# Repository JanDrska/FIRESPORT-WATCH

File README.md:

# FIRESPORT-WATCH
OpenSource project based on arduino which allows better time measuring and adds some extras features.

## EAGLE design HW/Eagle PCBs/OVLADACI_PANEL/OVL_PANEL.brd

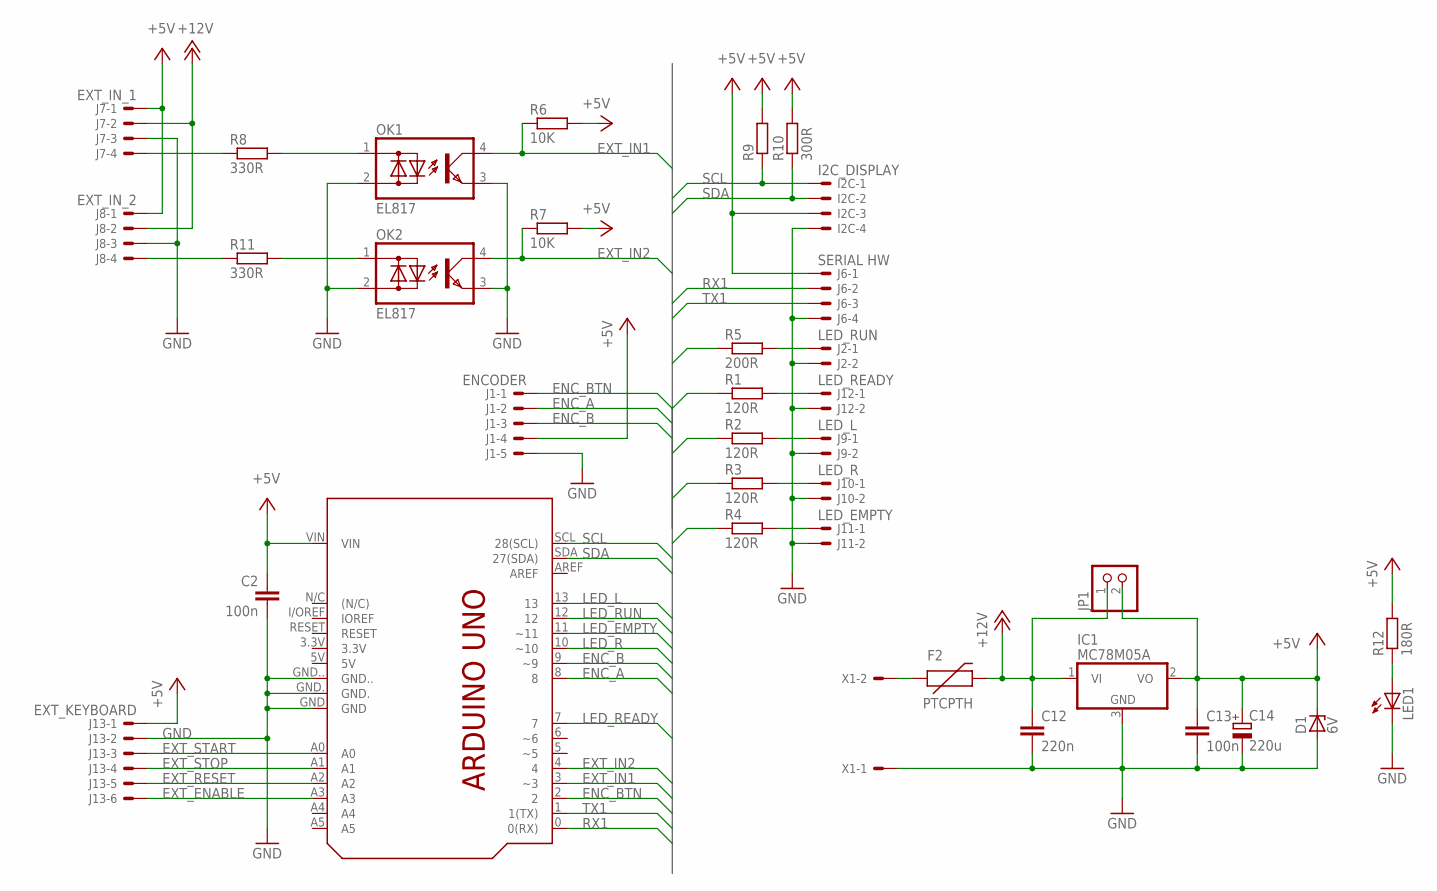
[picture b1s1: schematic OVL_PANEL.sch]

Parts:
C2, C13: 100n; C0603
C12: 220n; C0603
C14: 220u; E2,5-6E
D1: 6V; SMB
F2: PTCPTH; PTC
I2C: I2C_DISPLAY; 6410-04
IC1: MC78M05A; TO252
J1: ENCODER; 6410-05
J2: LED_RUN; 6410-02
J6: SERIAL HW; 6410-04
J7: EXT_IN_1; 6410-04
J8: EXT_IN_2; 6410-04
J9: LED_L; 6410-02
J10: LED_R; 6410-02
J11: LED_EMPTY; 6410-02
J12: LED_READY; 6410-02
J13: EXT_KEYBOARD; 6410-06
JP1: PINHD-1X2; 1X02
LED1: LEDCHIP-LED0603; CHIP-LED0603
OK1, OK2: EL817; DIL04
PCB1: ARDUINO_UNO
R1, R2, R3, R4: 120R; R0603
R5: 200R; R0603
R6, R7: 10K; R0603
R8, R11: 330R; R0603
R9: R-EU_R0603; R0603
R10: 300R; R0603
R12: 180R; R0603
X1: 22-23-2021

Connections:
+5V: C2.1, C13.1, C14.+, D1.C, I2C.3, IC1.2 (VO), J1.4, J6.1, J7.1, J8.1, J13.1, JP1.2, PCB1.VIN, R6.2, R7.2, R9.2, R10.2, R12.2
+12V: C12.1, F2.P$2 (2), IC1.1 (VI), J7.2, J8.2, JP1.1
ENC_A: J1.2, PCB1.8
ENC_B: J1.3, PCB1.9 (~9)
ENC_BTN: J1.1, PCB1.2
EXT_ENABLE: J13.6, PCB1.A3
EXT_IN1: OK1.4 (C), PCB1.3 (~3), R6.1
EXT_IN2: OK2.4 (C), PCB1.4, R7.1
EXT_RESET: J13.5, PCB1.A2
EXT_START: J13.3, PCB1.A0
EXT_STOP: J13.4, PCB1.A1
GND: C2.2, C12.2, C13.2, C14.-, D1.A, I2C.4, IC1.3 (GND), J1.5, J2.2, J6.4, J7.3, J8.3, J9.2, J10.2, J11.2, J12.2, J13.2, LED1.C, OK1.2 (AC2), OK1.3 (E), OK2.2 (AC2), OK2.3 (E), PCB1.GND, PCB1.GND., PCB1.GND.., X1.1
LED_EMPTY: PCB1.11 (~11), R4.1
LED_L: PCB1.13, R2.1
LED_R: PCB1.10 (~10), R3.1
LED_READY: PCB1.7, R1.1
LED_RUN: PCB1.12, R5.1
unnamed: J12.1, R1.2
unnamed: J2.1, R5.2
unnamed: J9.1, R2.2
unnamed: J10.1, R3.2
unnamed: J11.1, R4.2
unnamed: F2.P$1 (1), X1.2
unnamed: J7.4, R8.1
unnamed: J8.4, R11.1
unnamed: LED1.A, R12.1
unnamed: OK2.1 (AC1), R11.2
unnamed: OK1.1 (AC1), R8.2
RX1: J6.2, PCB1.0 (0(RX))
SCL: I2C.1, PCB1.SCL (28(SCL)), R9.1
SDA: I2C.2, PCB1.SDA (27(SDA)), R10.1
TX1: J6.3, PCB1.1 (1(TX))

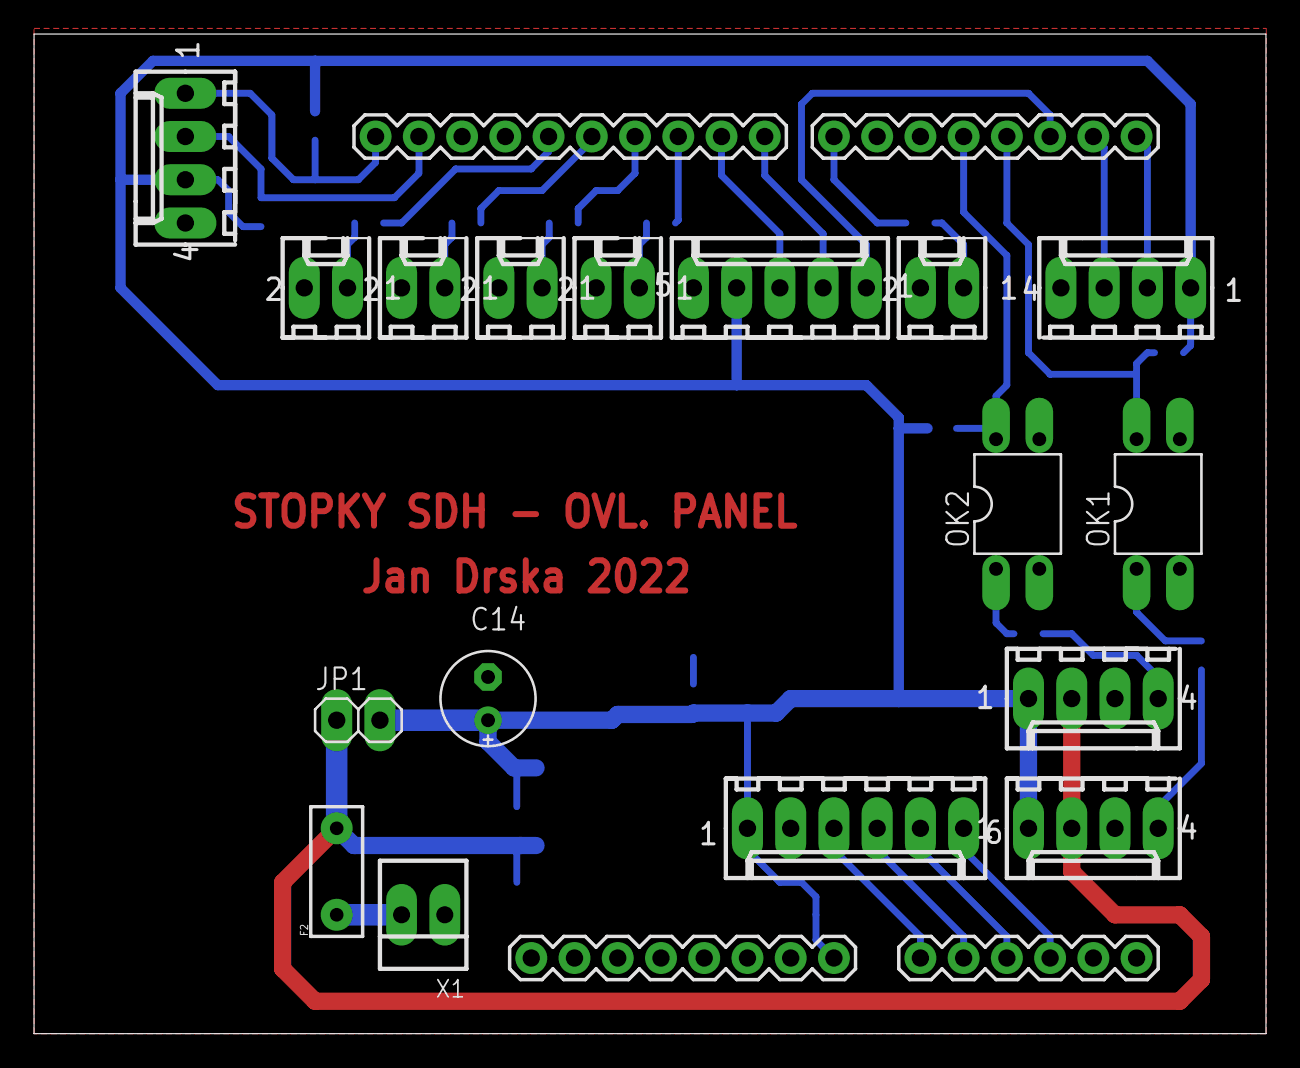
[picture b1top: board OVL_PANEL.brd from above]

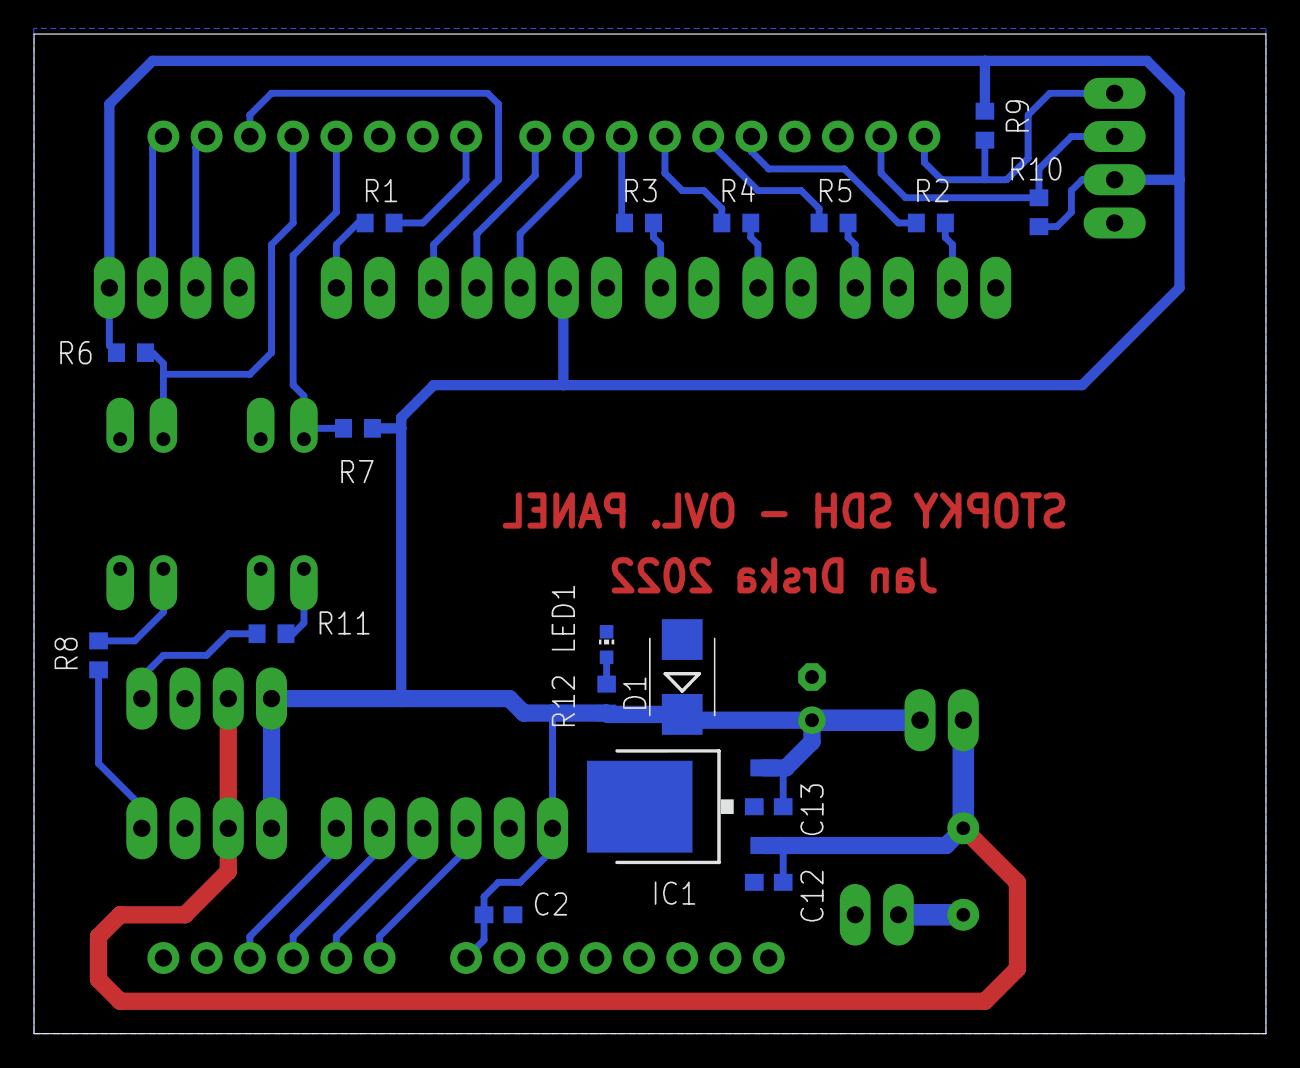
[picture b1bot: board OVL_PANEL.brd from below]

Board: 2 copper layers, 72.4 x 58.7 mm, 36 parts (18 on the bottom side), 32 nets.

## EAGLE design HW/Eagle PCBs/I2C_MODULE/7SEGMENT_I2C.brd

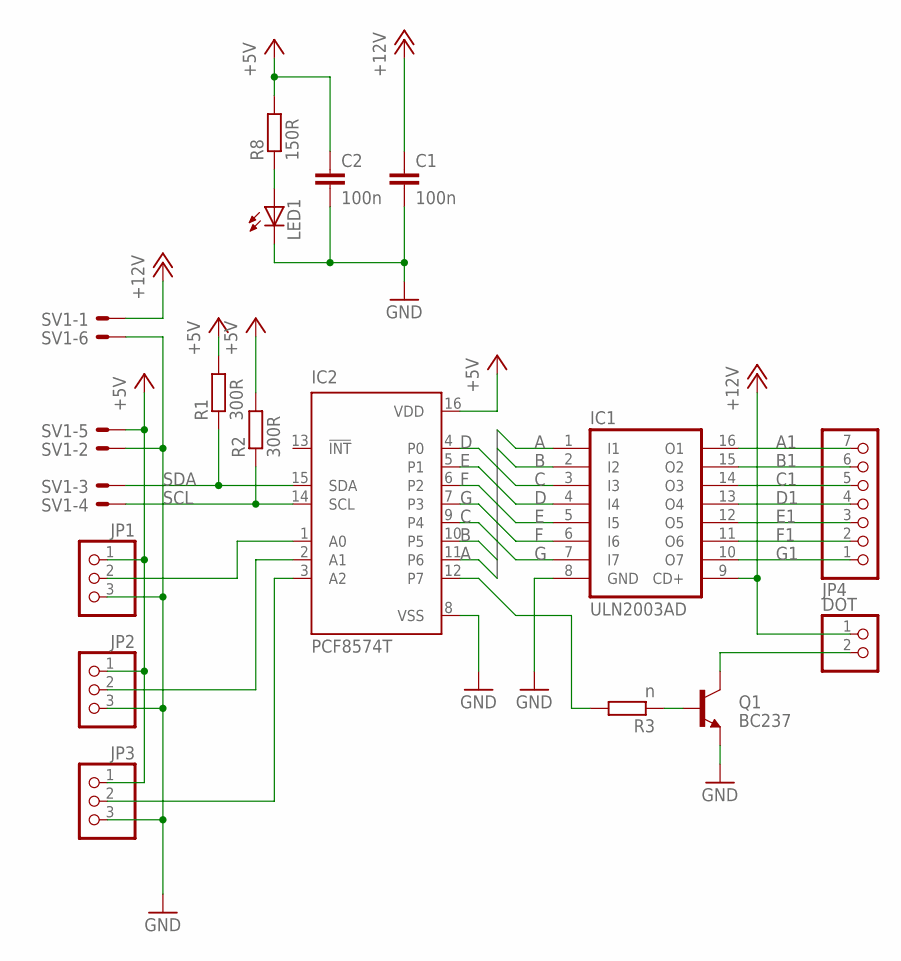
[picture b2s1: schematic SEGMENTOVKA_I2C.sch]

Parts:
C1, C2: 100n; C0603
DOT: PINHD-1X2; 1X02
IC1: ULN2003AD; SO16
IC2: PCF8574T; SO16W
JP1, JP2, JP3: PINHD-1X3; 1X03
JP4: PINHD-1X7; 1X07
LED1: LEDCHIP-LED0603; CHIP-LED0603
Q1: BC237; TO92
R1, R2: 300R; R0603
R3: n; R0603
R8: 150R; R0603
SV1: ML6E; ML6

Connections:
+5V: C2.1, IC2.16 (VDD), JP1.1, JP2.1, JP3.1, R1.2, R2.2, R8.2, SV1.5
+12V: C1.1, DOT.1, IC1.9 (CD+), SV1.1
A: IC1.1 (I1), IC2.11 (P6)
A1: IC1.16 (O1), JP4.7
B: IC1.2 (I2), IC2.10 (P5)
B1: IC1.15 (O2), JP4.6
C: IC1.3 (I3), IC2.9 (P4)
C1: IC1.14 (O3), JP4.5
D: IC1.4 (I4), IC2.4 (P0)
D1: IC1.13 (O4), JP4.4
E: IC1.5 (I5), IC2.5 (P1)
E1: IC1.12 (O5), JP4.3
F: IC1.6 (I6), IC2.6 (P2)
F1: IC1.11 (O6), JP4.2
G: IC1.7 (I7), IC2.7 (P3)
G1: IC1.10 (O7), JP4.1
GND: C1.2, C2.2, IC1.8 (GND), IC2.8 (VSS), JP1.3, JP2.3, JP3.3, LED1.C, Q1.1 (E), SV1.2, SV1.6
unnamed: DOT.2, Q1.3 (C)
unnamed: Q1.2 (B), R3.1
unnamed: IC2.12 (P7), R3.2
unnamed: IC2.1 (A0), JP1.2
unnamed: IC2.2 (A1), JP2.2
unnamed: IC2.3 (A2), JP3.2
unnamed: LED1.A, R8.1
SCL: IC2.14 (SCL), R2.1, SV1.4
SDA: IC2.15 (SDA), R1.1, SV1.3

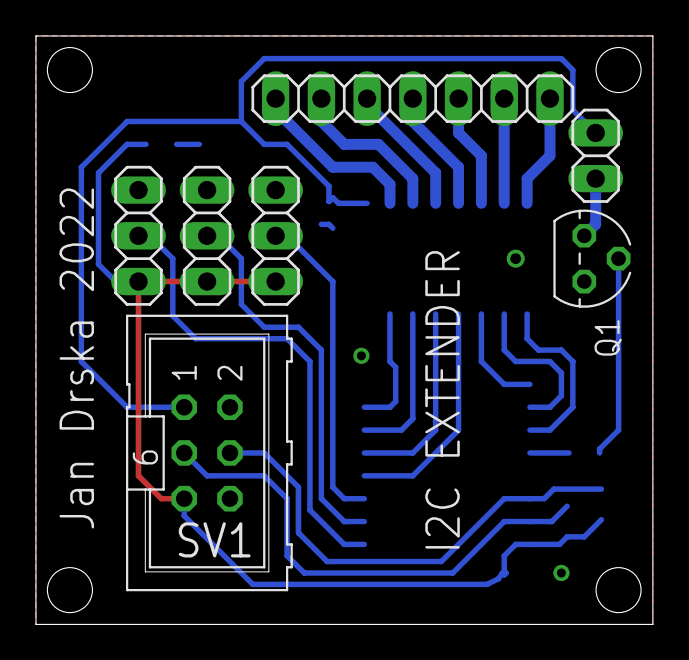
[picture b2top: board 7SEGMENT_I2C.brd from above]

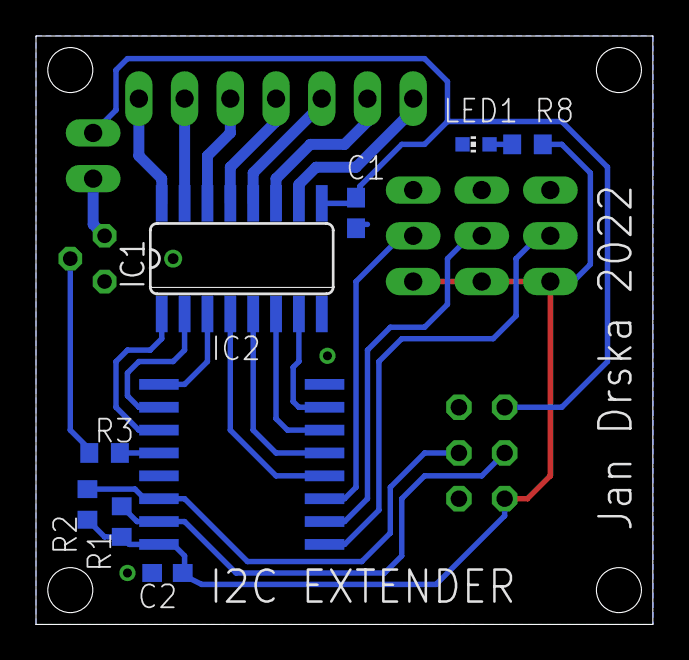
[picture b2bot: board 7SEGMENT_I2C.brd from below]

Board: 2 copper layers, 34.3 x 32.7 mm, 16 parts (9 on the bottom side), 26 nets.

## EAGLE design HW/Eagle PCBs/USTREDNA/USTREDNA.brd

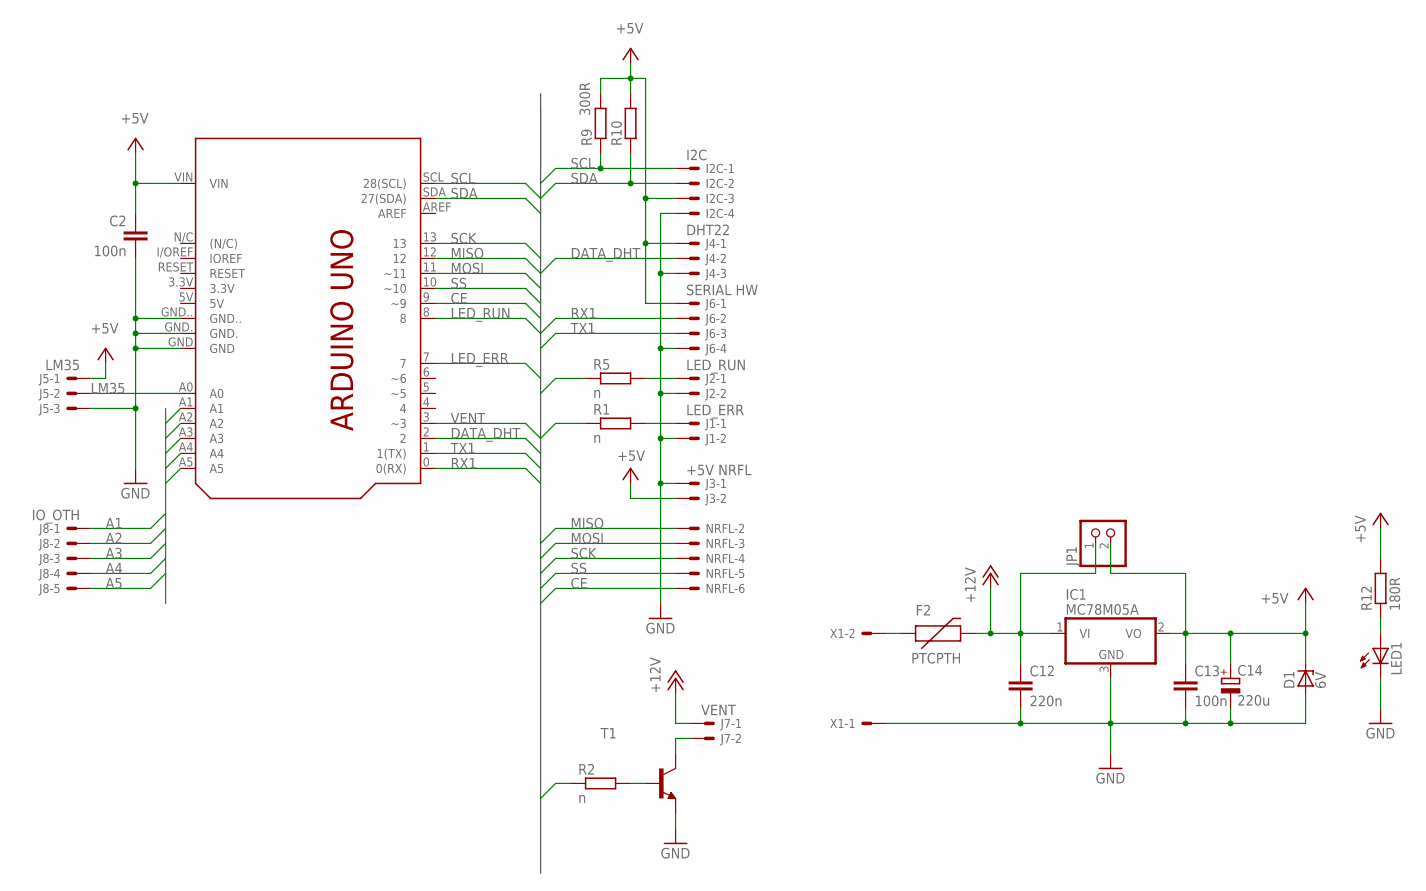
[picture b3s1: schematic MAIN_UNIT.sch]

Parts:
C2, C13: 100n; C0603
C12: 220n; C0603
C14: 220u; E2,5-6E
D1: 6V; SMB
F2: PTCPTH; PTC
I2C: I2C; 6410-04
IC1: MC78M05A; TO252
J1: LED_ERR; 6410-02
J2: LED_RUN; 6410-02
J3: +5V NRFL; 6410-02
J4: DHT22; 6410-03
J5: LM35; 6410-03
J6: SERIAL HW; 6410-04
J7: VENT; 6410-02
J8: IO_OTH; 6410-05
JP1: PINHD-1X2; 1X02
LED1: LEDCHIP-LED0603; CHIP-LED0603
NRFL: NRFL; 6410-06
PCB1: ARDUINO_UNO
R1, R2, R5: n; R0603
R9: R-EU_R0603; R0603
R10: 300R; R0603
R12: 180R; R0603
T1: -NPN-SOT223; SOT223
X1: 22-23-2021

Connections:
+5V: C2.1, C13.1, C14.+, D1.C, I2C.3, IC1.2 (VO), J3.2, J4.1, J5.1, J6.1, JP1.2, PCB1.VIN, R9.2, R10.2, R12.2
+12V: C12.1, F2.P$2 (2), IC1.1 (VI), J7.1, JP1.1
A1: J8.1, PCB1.A1
A2: J8.2, PCB1.A2
A3: J8.3, PCB1.A3
A4: J8.4, PCB1.A4
A5: J8.5, PCB1.A5
CE: NRFL.6, PCB1.9 (~9)
DATA_DHT: J4.2, PCB1.2
GND: C2.2, C12.2, C13.2, C14.-, D1.A, I2C.4, IC1.3 (GND), J1.2, J2.2, J3.1, J4.3, J5.3, J6.4, LED1.C, PCB1.GND, PCB1.GND., PCB1.GND.., T1.3 (E), X1.1
LED_ERR: PCB1.7, R1.1
LED_RUN: PCB1.8, R5.1
LM35: J5.2, PCB1.A0
MISO: NRFL.2, PCB1.12
MOSI: NRFL.3, PCB1.11 (~11)
unnamed: J1.1, R1.2
unnamed: R2.2, T1.1 (B)
unnamed: J2.1, R5.2
unnamed: J7.2, T1.4 (C)
unnamed: F2.P$1 (1), X1.2
unnamed: LED1.A, R12.1
RX1: J6.2, PCB1.0 (0(RX))
SCK: NRFL.4, PCB1.13
SCL: I2C.1, PCB1.SCL (28(SCL)), R9.1
SDA: I2C.2, PCB1.SDA (27(SDA)), R10.1
SS: NRFL.5, PCB1.10 (~10)
TX1: J6.3, PCB1.1 (1(TX))
VENT: PCB1.3 (~3), R2.1

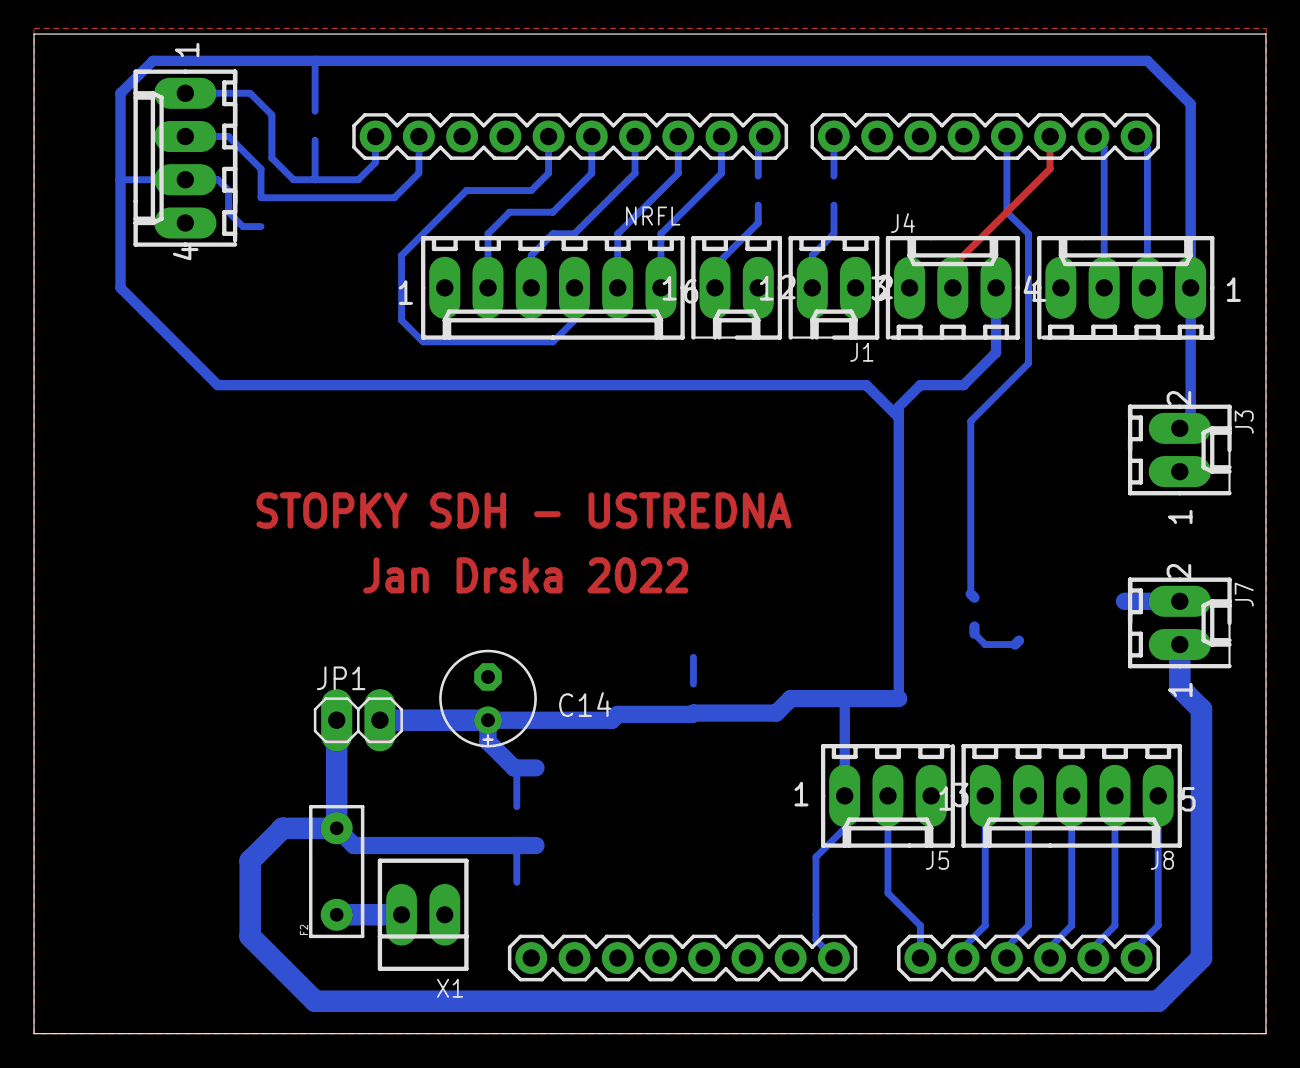
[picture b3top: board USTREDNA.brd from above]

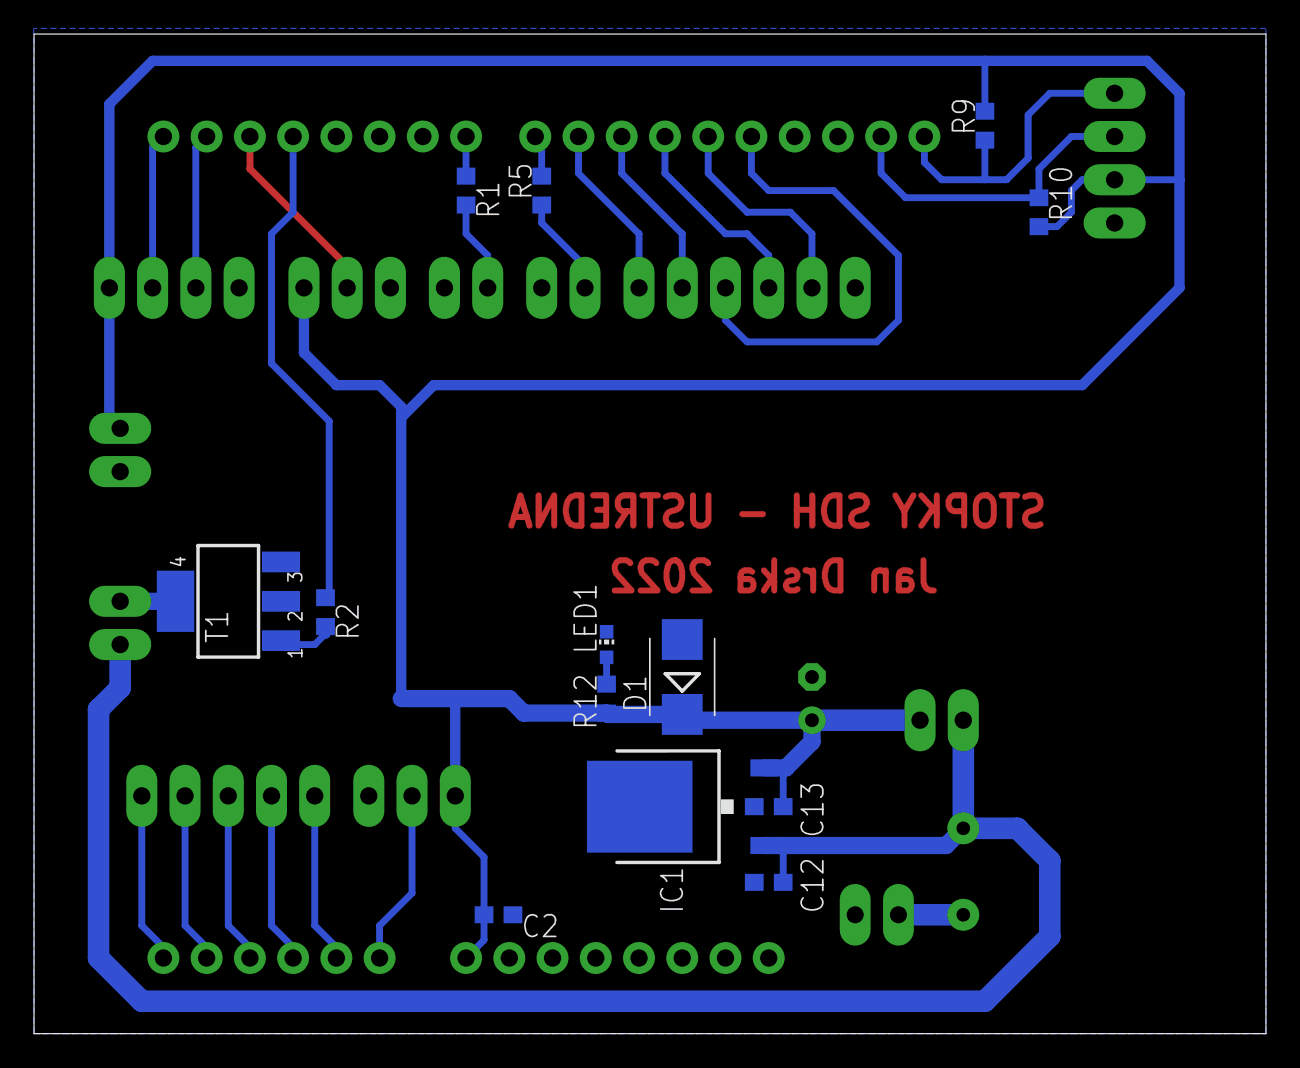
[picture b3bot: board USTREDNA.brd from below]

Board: 2 copper layers, 72.4 x 58.7 mm, 28 parts (13 on the bottom side), 28 nets.

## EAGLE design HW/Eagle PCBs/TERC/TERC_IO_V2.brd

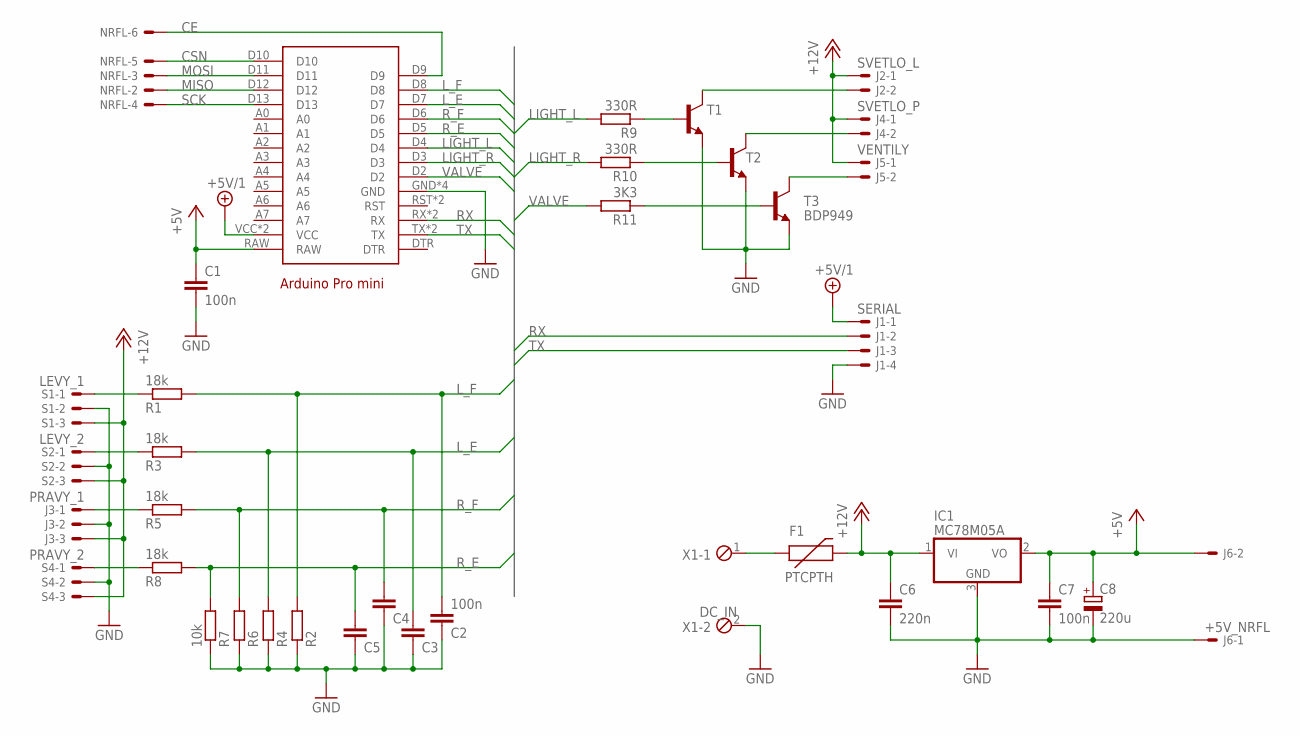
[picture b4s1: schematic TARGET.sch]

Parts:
ARDUINO1: ARDUINO_PRO_MINI
C1, C2, C7: 100n; C0603
C3, C4, C5: C-EUC0603; C0603
C6: 220n; C0603
C8: 220u; E2,5-6E
F1: PTCPTH; PTC
IC1: MC78M05A; TO252
J1: SERIAL; 6410-04
J2: SVETLO_L; 6410-02
J3: PRAVY_1; 6410-03
J4: SVETLO_P; 6410-02
J5: VENTILY; 6410-02
J6: +5V_NRFL; 6410-02
NRFL: NRFL; 6410-06
R1, R3, R5, R8: 18k; R0603
R2, R4, R6: R-EU_R0603; R0603
R7: 10k; R0603
R9, R10: 330R; R0603
R11: 3K3; R0603
S1: LEVY_1; 6410-03
S2: LEVY_2; 6410-03
S4: PRAVY_2; 6410-03
T1, T3: BDP949; SOT223
T2: -NPN-SOT223; SOT223
X1: DC_IN; 2POL254

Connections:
+5V: ARDUINO1.RAW, C1.1, C7.1, C8.+, IC1.2 (VO), J6.2
+5V/1: ARDUINO1.VCC, ARDUINO1.VCC@1 (VCC), J1.1
+12V: C6.1, F1.P$2 (2), IC1.1 (VI), J2.1, J3.3, J4.1, J5.1, S1.3, S2.3, S4.3
CE: ARDUINO1.D9, NRFL.6
CSN: ARDUINO1.D10, NRFL.5
GND: ARDUINO1.GND, ARDUINO1.GND@1 (GND), ARDUINO1.GND@2 (GND), ARDUINO1.GND@3 (GND), C1.2, C2.1, C3.1, C4.1, C5.1, C6.2, C7.2, C8.-, IC1.3 (GND), J1.4, J3.2, J6.1, R2.1, R4.1, R6.1, R7.1, S1.2, S2.2, S4.2, T1.3 (E), T2.3 (E), T3.3 (E), X1.2
LIGHT_L: ARDUINO1.D4, R9.2
LIGHT_R: ARDUINO1.D3, R10.2
L_E: ARDUINO1.D7, C3.2, R3.2, R4.2
L_F: ARDUINO1.D8, C2.2, R1.2, R2.2
MISO: ARDUINO1.D12, NRFL.2
MOSI: ARDUINO1.D11, NRFL.3
unnamed: R1.1, S1.1
unnamed: R3.1, S2.1
unnamed: R8.1, S4.1
unnamed: J3.1, R5.1
unnamed: F1.P$1 (1), X1.1
unnamed: J2.2, T1.4 (C)
unnamed: J4.2, T2.4 (C)
unnamed: J5.2, T3.4 (C)
unnamed: R11.1, T3.1 (B)
unnamed: R10.1, T2.1 (B)
unnamed: R9.1, T1.1 (B)
RX: ARDUINO1.RX, ARDUINO1.RX@1 (RX), J1.2
R_E: ARDUINO1.D5, C5.2, R7.2, R8.2
R_F: ARDUINO1.D6, C4.2, R5.2, R6.2
SCK: ARDUINO1.D13, NRFL.4
TX: ARDUINO1.TX, ARDUINO1.TX@1 (TX), J1.3
VALVE: ARDUINO1.D2, R11.2

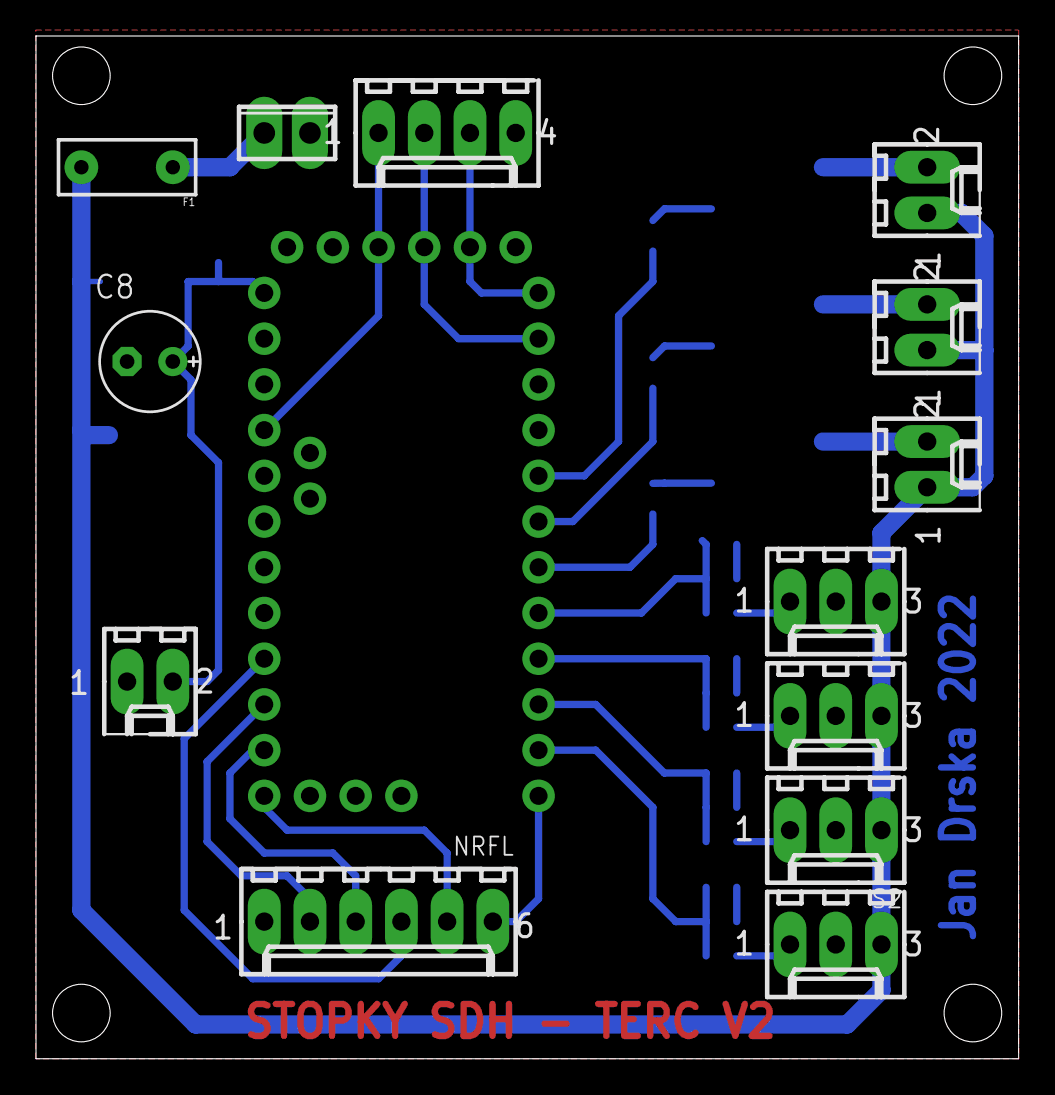
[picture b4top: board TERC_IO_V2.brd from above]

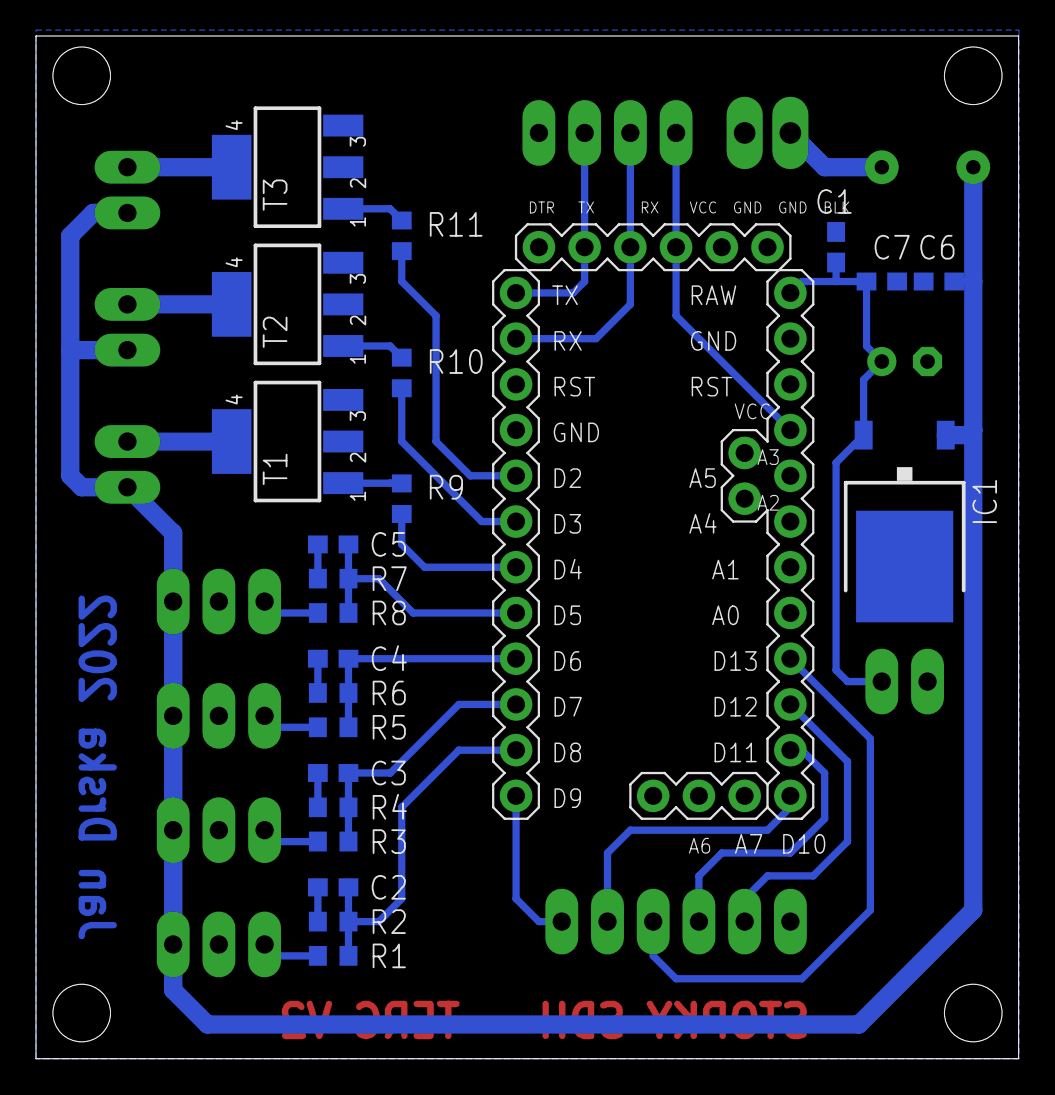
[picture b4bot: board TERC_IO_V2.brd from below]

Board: 2 copper layers, 54.6 x 56.8 mm, 36 parts (23 on the bottom side), 29 nets.

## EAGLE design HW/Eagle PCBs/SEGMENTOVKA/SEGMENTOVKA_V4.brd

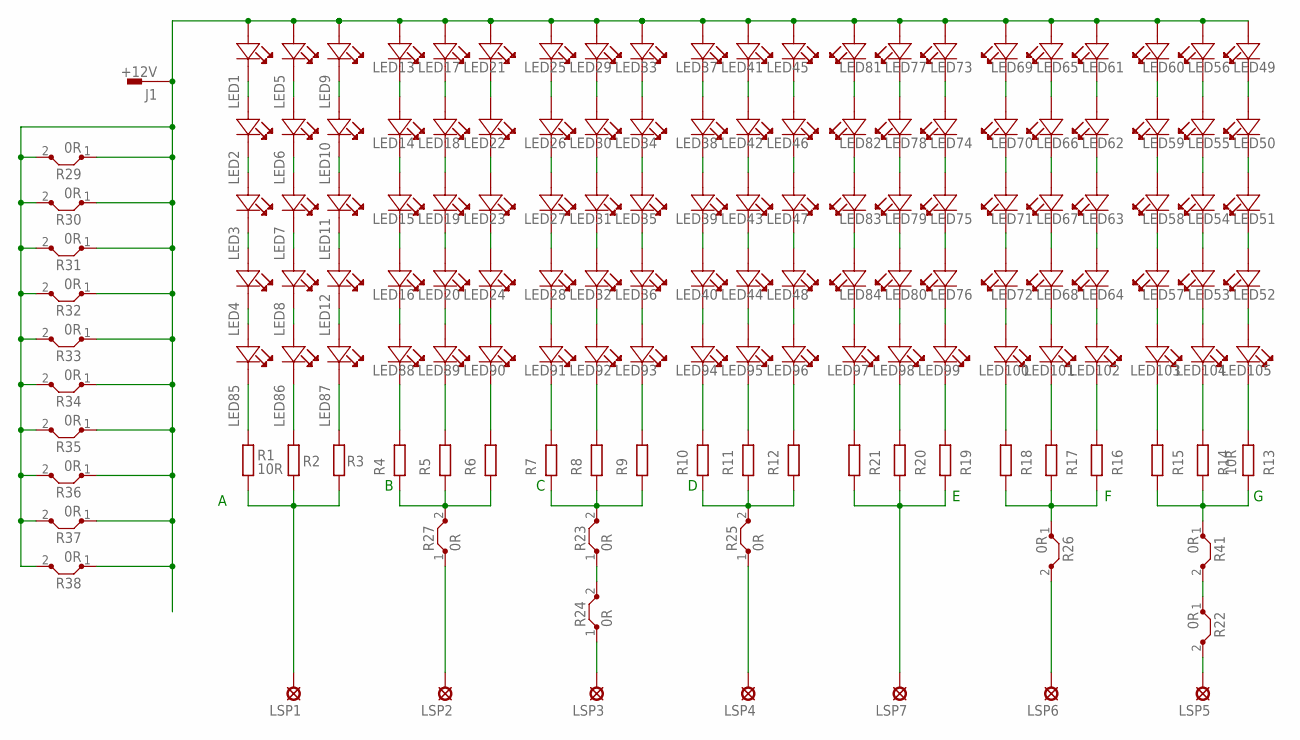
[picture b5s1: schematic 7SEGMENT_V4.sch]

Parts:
J1: +12V; F061.040
LED1, LED2, LED3, LED4, LED5, LED6, LED7, LED8, LED9, LED10, LED11, LED12, LED13, LED14, LED15, LED16, LED17, LED18, LED19, LED20, LED21, LED22, LED23, LED24, LED25, LED26, LED27, LED28, LED29, LED30, LED31, LED32, LED33, LED34, LED35, LED36, LED37, LED38, LED39, LED40, LED41, LED42, LED43, LED44, LED45, LED46, LED47, LED48, LED49, LED50, LED51, LED52, LED53, LED54, LED55, LED56, LED57, LED58, LED59, LED60, LED61, LED62, LED63, LED64, LED65, LED66, LED67, LED68, LED69, LED70, LED71, LED72, LED73, LED74, LED75, LED76, LED77, LED78, LED79, LED80, LED81, LED82, LED83, LED84, LED85, LED86, LED87, LED88, LED89, LED90, LED91, LED92, LED93, LED94, LED95, LED96, LED97, LED98, LED99, LED100, LED101, LED102, LED103, LED104, LED105: OF-SMD2835Y; LED_OF-SMD2835Y
LSP1: A; MCS08
LSP2: B; MCS08
LSP3: C; MCS08
LSP4: D; MCS08
LSP5: G; MCS08
LSP6: F; MCS08
LSP7: E; MCS08
R1, R13: 10R; R0603
R2, R3, R4, R5, R6, R7, R8, R9, R10, R11, R12, R14, R15, R16, R17, R18, R19, R20, R21: R-EU_R0603; R0603
R22, R23, R24, R25, R26, R27, R29, R30, R31, R32, R33, R34, R35, R36, R37, R38, R41: 0R; 05

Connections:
+12V: J1.A1 (1), LED1.1 (A), LED5.1 (A), LED9.1 (A), LED13.1 (A), LED17.1 (A), LED21.1 (A), LED25.1 (A), LED29.1 (A), LED33.1 (A), LED37.1 (A), LED41.1 (A), LED45.1 (A), LED49.1 (A), LED56.1 (A), LED60.1 (A), LED61.1 (A), LED65.1 (A), LED69.1 (A), LED73.1 (A), LED77.1 (A), LED81.1 (A), R29.1, R29.2, R30.1, R30.2, R31.1, R31.2, R32.1, R32.2, R33.1, R33.2, R34.1, R34.2, R35.1, R35.2, R36.1, R36.2, R37.1, R37.2, R38.1, R38.2
unnamed: LED1.2 (C), LED2.1 (A)
unnamed: LED2.2 (C), LED3.1 (A)
unnamed: LED3.2 (C), LED4.1 (A)
unnamed: LED5.2 (C), LED6.1 (A)
unnamed: LED6.2 (C), LED7.1 (A)
unnamed: LED7.2 (C), LED8.1 (A)
unnamed: LED9.2 (C), LED10.1 (A)
unnamed: LED10.2 (C), LED11.1 (A)
unnamed: LED11.2 (C), LED12.1 (A)
unnamed: LED13.2 (C), LED14.1 (A)
unnamed: LED14.2 (C), LED15.1 (A)
unnamed: LED15.2 (C), LED16.1 (A)
unnamed: LED17.2 (C), LED18.1 (A)
unnamed: LED18.2 (C), LED19.1 (A)
unnamed: LED19.2 (C), LED20.1 (A)
unnamed: LED21.2 (C), LED22.1 (A)
unnamed: LED22.2 (C), LED23.1 (A)
unnamed: LED23.2 (C), LED24.1 (A)
unnamed: LED25.2 (C), LED26.1 (A)
unnamed: LED26.2 (C), LED27.1 (A)
unnamed: LED27.2 (C), LED28.1 (A)
unnamed: LED29.2 (C), LED30.1 (A)
unnamed: LED30.2 (C), LED31.1 (A)
unnamed: LED31.2 (C), LED32.1 (A)
unnamed: LED33.2 (C), LED34.1 (A)
unnamed: LED34.2 (C), LED35.1 (A)
unnamed: LED35.2 (C), LED36.1 (A)
unnamed: LED37.2 (C), LED38.1 (A)
unnamed: LED38.2 (C), LED39.1 (A)
unnamed: LED39.2 (C), LED40.1 (A)
unnamed: LED41.2 (C), LED42.1 (A)
unnamed: LED42.2 (C), LED43.1 (A)
unnamed: LED43.2 (C), LED44.1 (A)
unnamed: LED45.2 (C), LED46.1 (A)
unnamed: LED46.2 (C), LED47.1 (A)
unnamed: LED47.2 (C), LED48.1 (A)
unnamed: LED49.2 (C), LED50.1 (A)
unnamed: LED85.2 (C), R1.2
unnamed: LED53.1 (A), LED54.2 (C)
unnamed: LED54.1 (A), LED55.2 (C)
unnamed: LSP5.MP, R22.2
unnamed: LED58.1 (A), LED59.2 (C)
unnamed: LED57.1 (A), LED58.2 (C)
unnamed: LED61.2 (C), LED62.1 (A)
unnamed: LED62.2 (C), LED63.1 (A)
unnamed: LED63.2 (C), LED64.1 (A)
unnamed: LED65.2 (C), LED66.1 (A)
unnamed: LED66.2 (C), LED67.1 (A)
unnamed: LED67.2 (C), LED68.1 (A)
unnamed: LED69.2 (C), LED70.1 (A)
unnamed: LED70.2 (C), LED71.1 (A)
unnamed: LED71.2 (C), LED72.1 (A)
unnamed: LED73.2 (C), LED74.1 (A)
unnamed: LED74.2 (C), LED75.1 (A)
unnamed: LED75.2 (C), LED76.1 (A)
unnamed: LED77.2 (C), LED78.1 (A)
unnamed: LED78.2 (C), LED79.1 (A)
unnamed: LED79.2 (C), LED80.1 (A)
unnamed: LED81.2 (C), LED82.1 (A)
unnamed: LED82.2 (C), LED83.1 (A)
unnamed: LED83.2 (C), LED84.1 (A)
unnamed: LED50.2 (C), LED51.1 (A)
unnamed: LED51.2 (C), LED52.1 (A)
unnamed: LED4.2 (C), LED85.1 (A)
unnamed: LED8.2 (C), LED86.1 (A)
unnamed: LED86.2 (C), R2.2
unnamed: LED87.2 (C), R3.2
unnamed: LED12.2 (C), LED87.1 (A)
unnamed: LED16.2 (C), LED88.1 (A)
unnamed: LED20.2 (C), LED89.1 (A)
unnamed: LED24.2 (C), LED90.1 (A)
unnamed: LED88.2 (C), R4.2
unnamed: LED89.2 (C), R5.2
unnamed: LED90.2 (C), R6.2
unnamed: LED28.2 (C), LED91.1 (A)
unnamed: LED32.2 (C), LED92.1 (A)
unnamed: LED55.1 (A), LED56.2 (C)
unnamed: LED59.1 (A), LED60.2 (C)
unnamed: LED36.2 (C), LED93.1 (A)
unnamed: LED40.2 (C), LED94.1 (A)
unnamed: LED44.2 (C), LED95.1 (A)
unnamed: LED48.2 (C), LED96.1 (A)
unnamed: LED84.2 (C), LED97.1 (A)
unnamed: LED80.2 (C), LED98.1 (A)
unnamed: LED76.2 (C), LED99.1 (A)
unnamed: R4.1, R5.1, R6.1, R27.2
unnamed: R7.1, R8.1, R9.1, R23.2
unnamed: R10.1, R11.1, R12.1, R25.2
unnamed: R22.1, R41.2
unnamed: R16.1, R17.1, R18.1, R26.1
unnamed: LSP1.MP, R1.1, R2.1, R3.1
unnamed: R13.1, R14.1, R15.1, R41.1
unnamed: LSP7.MP, R19.1, R20.1, R21.1
unnamed: LSP2.MP, R27.1
unnamed: LSP3.MP, R24.1
unnamed: LSP4.MP, R25.1
unnamed: R23.1, R24.2
unnamed: LSP6.MP, R26.2
unnamed: LED72.2 (C), LED100.1 (A)
unnamed: LED68.2 (C), LED101.1 (A)
unnamed: LED64.2 (C), LED102.1 (A)
unnamed: LED57.2 (C), LED103.1 (A)
unnamed: LED52.2 (C), LED105.1 (A)
unnamed: LED91.2 (C), R7.2
unnamed: LED92.2 (C), R8.2
unnamed: LED93.2 (C), R9.2
unnamed: LED94.2 (C), R10.2
unnamed: LED95.2 (C), R11.2
unnamed: LED96.2 (C), R12.2
unnamed: LED97.2 (C), R21.2
unnamed: LED98.2 (C), R20.2
unnamed: LED99.2 (C), R19.2
unnamed: LED100.2 (C), R18.2
unnamed: LED101.2 (C), R17.2
unnamed: LED102.2 (C), R16.2
unnamed: LED103.2 (C), R15.2
unnamed: LED104.2 (C), R14.2
unnamed: LED105.2 (C), R13.2
unnamed: LED53.2 (C), LED104.1 (A)

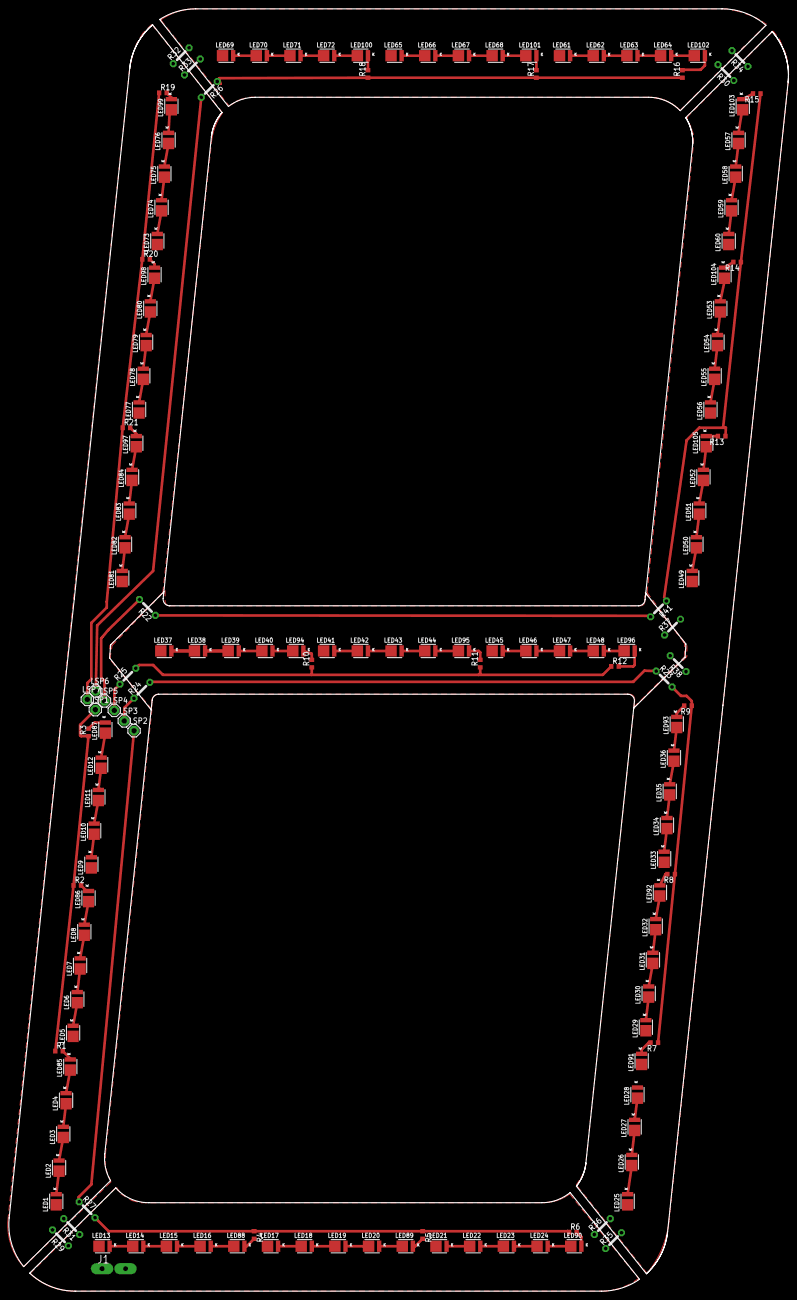
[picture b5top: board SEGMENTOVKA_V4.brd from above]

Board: 2 copper layers, 176.3 x 290.0 mm, 151 parts (0 on the bottom side), 120 nets.

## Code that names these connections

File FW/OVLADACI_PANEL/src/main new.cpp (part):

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#define E_Enable A3

// Enkoder
#define ENC_BTN 2
#define OutputA 8
#define OutputB 9

// Externi vstupy start
#define EXT_IN1 3 // moznost vyuziti preruseni
#define EXT_IN2 4

// Indikacni LED
#define LED_READY 7
#define LED_R 10
#define LED_L 13
#define LED_EMPTY 11
#define LED_RUN 12

// define text to display
const char menuPozSport[] PROGMEM = {"Pozarni sport"};  //Hlavni nabidka
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  lcd.backlight();
  lcd.clear();

  pinMode(LED_EMPTY, OUTPUT);
  pinMode(LED_R, OUTPUT);
  pinMode(LED_READY, OUTPUT);
  pinMode(LED_L, OUTPUT);

  Serial.begin(9600);

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

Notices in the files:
FW/OVLADACI_PANEL/src/main new.cpp:
include "CMBMenu.hpp"  //Copyright (C) 2022  Michael Bernhard
parts and their libraries:
SparkFun: Licensing: CC v3.0 Share-Alike You are welcome to use this library for commercial purposes.
